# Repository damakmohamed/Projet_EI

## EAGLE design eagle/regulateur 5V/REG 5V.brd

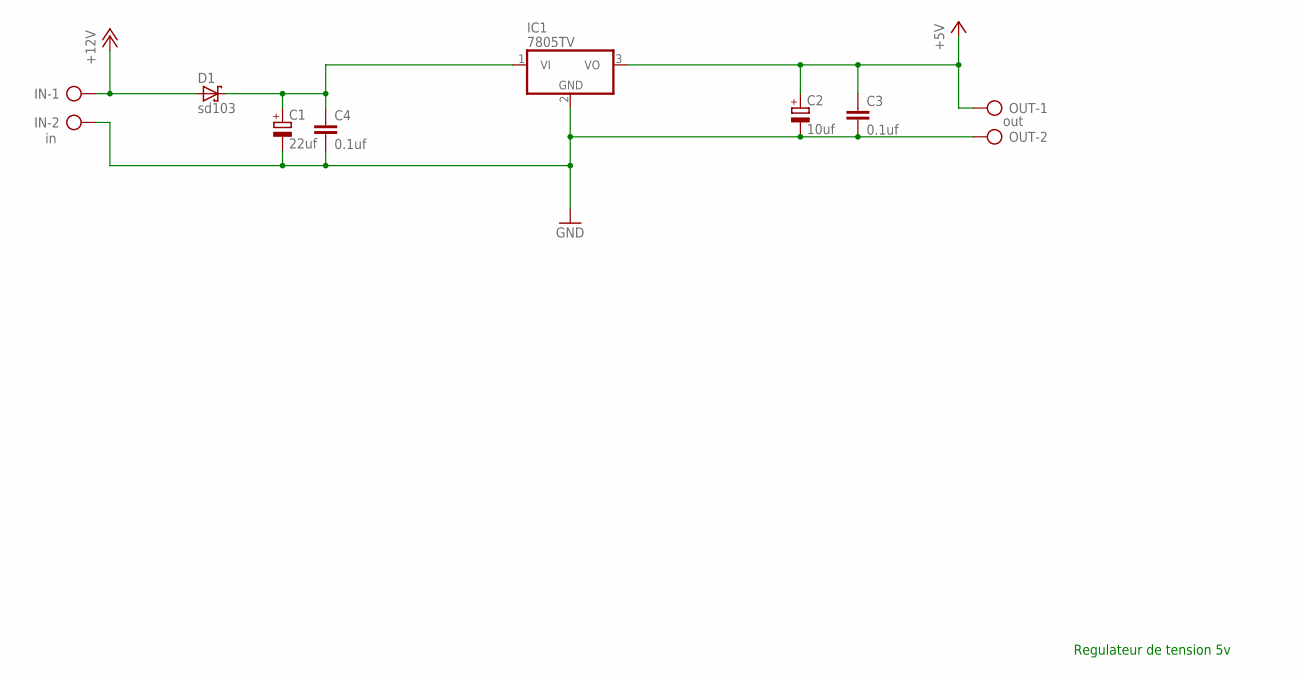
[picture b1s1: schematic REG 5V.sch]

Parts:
C1: 22uf; E2,5-5
C2: 10uf; E2,5-5
C3, C4: 0.1uf; C025-024X044
D1: sd103; DIODE_DO35-7
IC1: 7805TV; TO220V
IN: in; AK500/2
OUT: out; AK500/2

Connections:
+5V: C2.+, C3.1, IC1.3 (VO), OUT.1
+12V: D1.A (C), IN.1
GND: C1.-, C2.-, C3.2, C4.2, IC1.2 (GND), IN.2, OUT.2
unnamed: C1.+, C4.1, D1.C (A), IC1.1 (VI)

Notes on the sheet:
Regulateur de tension 5v

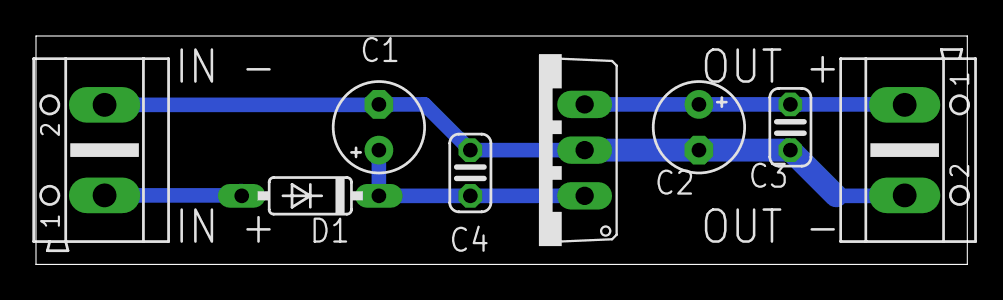
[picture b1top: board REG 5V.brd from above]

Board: 2 copper layers, 51.7 x 12.7 mm, 8 parts (0 on the bottom side), 4 nets.

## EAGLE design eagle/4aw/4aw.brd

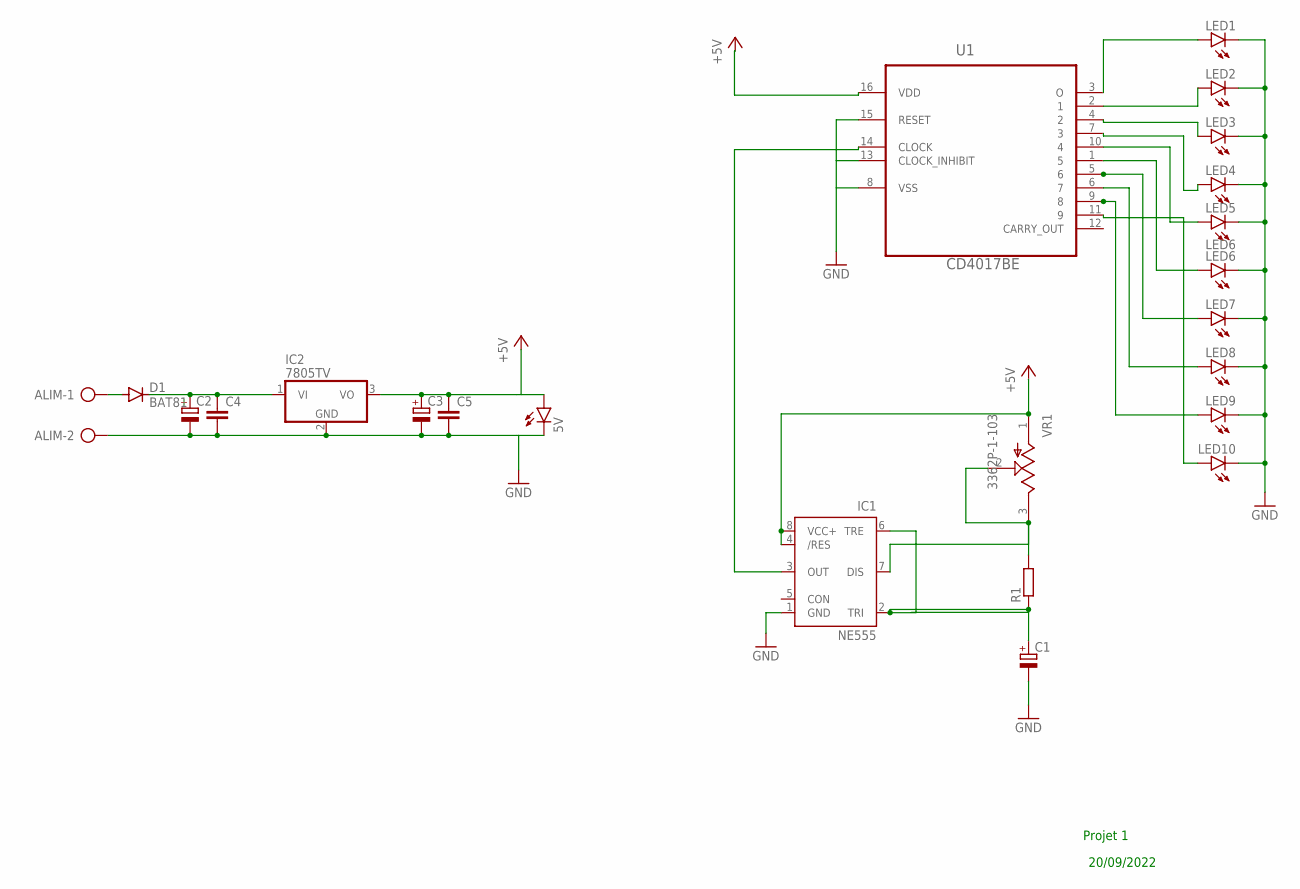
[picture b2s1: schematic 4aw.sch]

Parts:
5V: LED3MM
ALIM: AK500/2
C1, C2, C3: CPOL-EUE2.5-5; E2,5-5
C4, C5: C-EU050-024X044; C050-024X044
D1: BAT81; DO34-7
IC1: NE555; DIL-08
IC2: 7805TV; TO220V
LED1, LED2, LED3, LED4, LED5, LED7, LED8, LED9, LED10: LED5MM
LED6: LED6; LED5MM
R1: R-EU_0207/10; 0207/10
U1: CD4017BE; DIP254P762X508-16
VR1: 3362P-1-103; TRIM_3362P-1-103

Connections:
+5V: 5V.A, C3.+, C5.1, IC1.4 (/RES), IC1.8 (VCC+), IC2.3 (VO), U1.16 (VDD), VR1.1 (CCW)
GND: 5V.K (C), ALIM.2, C1.-, C2.-, C3.-, C4.2, C5.2, IC1.1 (GND), IC2.2 (GND), LED1.K (C), LED2.K (C), LED3.K (C), LED4.K (C), LED5.K (C), LED6.K (C), LED7.K (C), LED8.K (C), LED9.K (C), LED10.K (C), U1.8 (VSS), U1.13 (CLOCK_INHIBIT), U1.15 (RESET)
unnamed: LED4.A, U1.7 (3)
unnamed: LED5.A, U1.10 (4)
unnamed: LED6.A, U1.1 (5)
unnamed: LED10.A, U1.11 (9)
unnamed: LED8.A, U1.6 (7)
unnamed: IC1.3 (OUT), U1.14 (CLOCK)
unnamed: ALIM.1, D1.A
unnamed: LED3.A, U1.4 (2)
unnamed: LED2.A, U1.2 (1)
unnamed: LED1.A, U1.3 (O)
unnamed: C1.+, IC1.2 (TRI), IC1.6 (TRE), R1.1
unnamed: C2.+, C4.1, D1.C, IC2.1 (VI)
unnamed: LED7.A, U1.5 (6)
unnamed: IC1.7 (DIS), R1.2, VR1.2 (WIPER), VR1.3 (CW)
unnamed: LED9.A, U1.9 (8)

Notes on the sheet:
Projet 1
20/09/2022

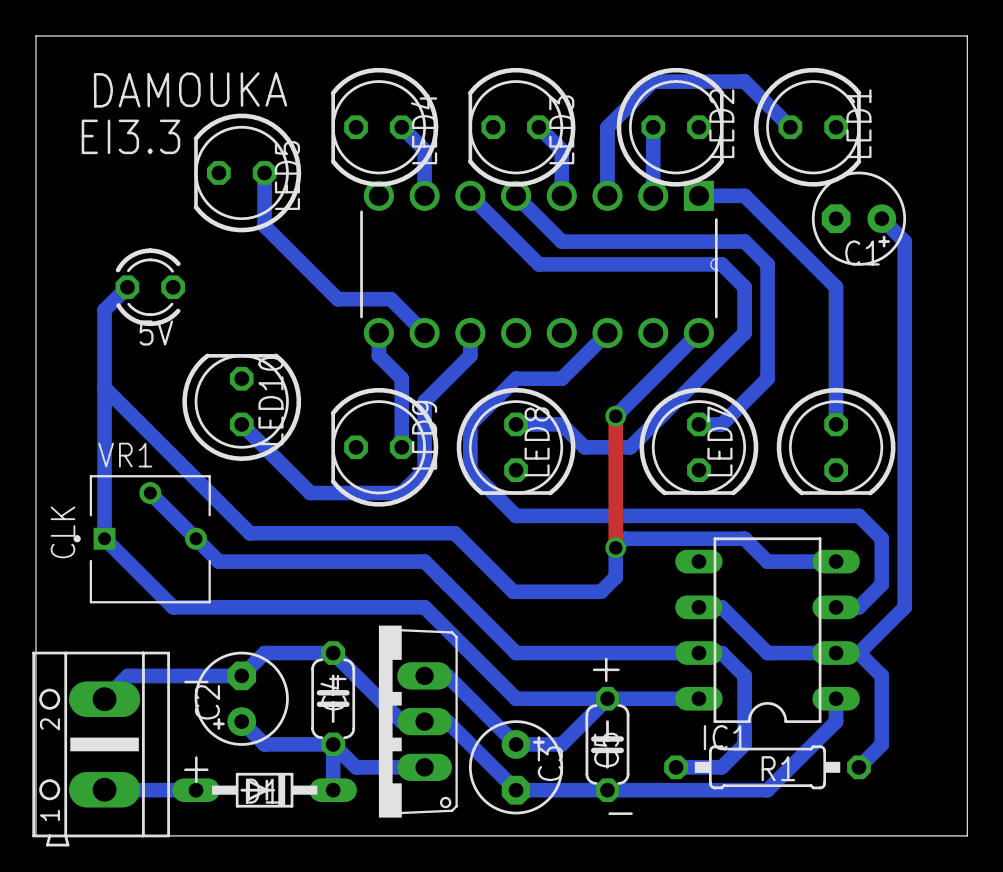
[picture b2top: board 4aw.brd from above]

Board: 2 copper layers, 51.7 x 44.4 mm, 23 parts (0 on the bottom side), 17 nets.

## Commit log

2022-10-19 Create Robot tout terrain
